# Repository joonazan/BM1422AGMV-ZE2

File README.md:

# Magnetic position tracking

Code for finding the position of a magnetometer or a coil relative to electromagnets in a fixed arrangement.

The process consists of two phases: determining each magnet's field strength at the measuring device and computing the position of the measuring device based on that.

## Finding each magnet's field strength at the position of interest

The main problem is isolating a single magnet's field from the earth's magnetic field, noise and the other magnets. This is not possible with just one point of data. One has to have multiple points of measurement or a sequence of measurements.

This project drives each magnet with a different sine wave. One only has to isolate the correct frequency from the magnetic field measurements.

### On magnetometers

Magnetometers are very small and thus easy to attach and unobtrusive. They could even be part of some cyberpunk nail art. But it is hard to find a suitable one for this purpose. I suspect that is because they are mostly meant for mobile phones.

The BM1422AGMV-ZE2 is the best one I could find. It can be set up to measure with 14-bit accuracy at one kilohertz.

The accuracy directly affects the accuracy of the position. Note that the difference between a magnet's positive and negative peak gets smaller and smaller with distance, so only a small part of the scale may be in use at one time.

The sample rate affects latency and accuracy while moving. Think about the Discrete Fourier Transform. With eight samples one would get one frequency bucket per magnet, the bare minimum. With more samples noise is filtered out.

We know the phase of the sine waves, which may help do more with less samples. I haven't investigated this.

One more pain point of magnetometers reading the data. The BM1422AGMV-ZE only supports two different I²C addresses, so each pair of them takes up one bus. They only support a 400kHz clock, too, so the bus is saturated.

### Isolating the frequencies

The signal processing happens on the chip that reads the magnetometers, as it is computationally inexpensive and reduces the amount of data by an order of magnitude. The code for the microprocessor is in `magnetometer_peripheral`.

A magnetometer measures the magnetic field on three perpendicular axes. The readings are not centered around zero magnetic field and changing the hardware in the slightest offsets them. Because of that, we cannot compute the unfiltered field strength with the Pythagorean Theorem. Each axis is filtered separately and then combined. This happens in `field_strength.h`.

The filtering is done using an algorithm that keeps a single DFT bucket up to date. Updating the bucket based on a new sample is O(1) regardless of DFT size. The buckets can be centered around any value but their window width depends on DFT size as usual. "The sliding DFT" (IEEE Signal Processing Magazine, April 2003) is a very detailed and readable explanation of the algorithm.

### Using a coil instead?

The receivers could be coils. Coils are larger than magnetometers and can have a bit more personality. However, with the correct circuit, they are not limited by a sample rate. That means that they can receive very high frequencies, which means low latency and low noise.

## Generating sines

`sine_pwm_no_arduino` contains the code that I've used on my Arduino Uno to generate sine waves via PWM. `flash.sh` is what I used to flash. The commands should be pretty straightforward to adapt to any platform.

I don't use the Arduino IDE because its compiler flags prevent me from generating a sine table in a sane way. `sine_pwm` is the same but uses ugly templates for sine table generation.

Both versions use Timer 0 and 2 and fire 250 000 interrupts per second to get very high frequency PWM. That may interfere with using the Arduino for other purposes.

The output needs to be smoothed with a low-pass filter and amplified.

A sine generator circuit could be used instead but it probably wouldn't even be cheaper than a cheap SoC. When using coils as receivers, a sine circuit is superior because this method can only go up to about 1 kHz with good quality.

## Finding the position

A point is uniquely determined by its distance from n points, where n is the number of dimensions plus one. For example in two dimensions two circles can intersect at two points, but three different circles can only intersect at one point.

`amplitude_to_position` is used to test and compare different algorithms for finding the point from which the magnet's strengths were measured.

There would be a simple exact solution if the fields spread out in a sphere (as is the case with GPS). However, only magnetic monopoles would have a spherical field. The field of a coil has a circular cross-section but the equation for its radius is fourth-degree.

TODO insert image of field shape

The same testbed can also be used to automatically compare different placements of magnets and thus find an optimal placement for a given level of noise and placement constraints.

TODO Some kind of Gradient descent probably works but I haven't tried it yet
TODO What about partitioning the cube root of field strength space?

### What doesn't work

The following two methods work perfectly if the measurements are perfectly accurate. But for high accuracy in practice a method is required that reacts gracefully to error.

#### Space partitioning

Implemented in `octtree.rs`. Finds the smallest cube that contains points with the correct field strength for each magnet.

Split cubes into smaller cubes. Keep the cubes that are still good.

Bad because:

- Splitting the optimal cube creates two cubes that are rejected.
- Performance is relatively bad and unpredictable. May allocate a lot. Performance may be better with a depth-first traversal rather than breadth-first.

#### Slicing

Implemented in `slicer.rs`. Slices the problem into a bunch of very cheaply solved circle intersection problems, takes the slice with least error.

I define the *scale* as `1 / cbrt(field strength)`. That is how much you have to scale the field strength = 1 surface to get the surface for that field strength.

The biggest possible slope of the error (in scale) vs. z is `4 / cbrt(2)`, which occurs when moving up when directly above the pole of all four magnets. The best solution is of course the same or better.

Bad because:

- Can only support configurations where all magnets point the same way.
- The slices' solutions are not optimal. You can see in the illustration that the inner isosurfaces are further apart along the red line than the outer ones. So the error is proportional to change in radius only at height zero. 

There is still some hope for this if there is a way to find the best solution to a slice. Quality could be improved just by taking into account that increasing radius is cheaper higher up.

## Running the whole stack

The Arduino MKR Wifi 1010 can be flashed with the Arduino IDE. FastBLE and I2C_DMAC are required because the official ones can't be used asynchronously. FastBLE includes a part that needs to be flashed onto the ESP side of the board. See its README.

Two BM1422AGMV-ZE magnetometers with address select wired differently can be attached to pins 11 (SDA here) and 12 (SCL here). TODO update once the other two pins pairs are used as well. (Should make it detect what pins have a device on them)

TODO write about computer side after I've worked with it again

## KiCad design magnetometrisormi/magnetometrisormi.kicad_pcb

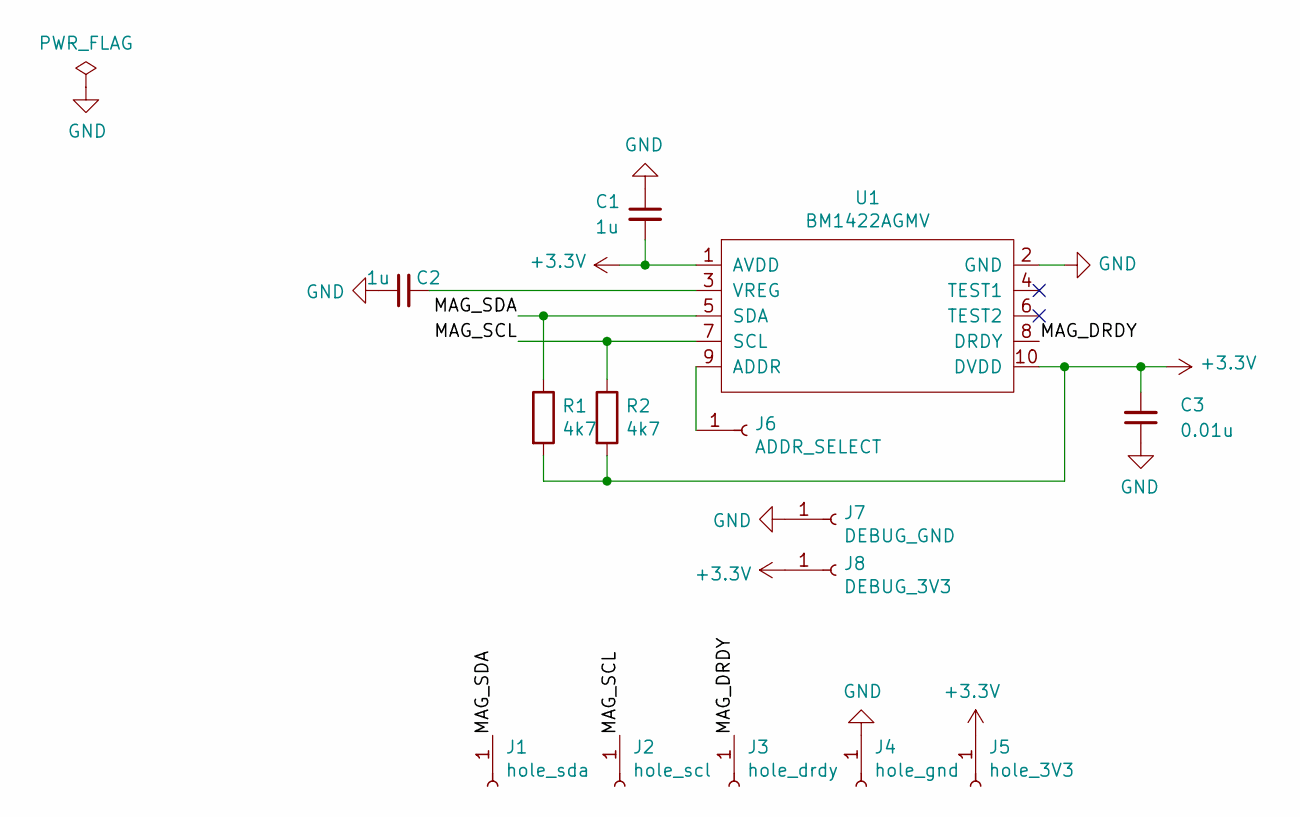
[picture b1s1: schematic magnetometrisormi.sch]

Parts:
C1, C2: 1u; C_0402_1005Metric
C3: 0.01u; C_0402_1005Metric
J1: hole_sda; hole
J2: hole_scl; hole
J3: hole_drdy; hole
J4: hole_gnd; hole
J5: hole_3V3; hole
J6: ADDR_SELECT; hole
J7: DEBUG_GND; hole
J8: DEBUG_3V3; hole
R1, R2: 4k7; R_0402_1005Metric
U1: BM1422AGMV; MLGA010V020A

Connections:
+3V3: C1.2, C3.2, J5.1, J8.1, R1.2, R2.2, U1.1 (AVDD), U1.10 (DVDD)
/MAG_DRDY: J3.1, U1.8 (DRDY)
/MAG_SCL: J2.1, R2.1, U1.7 (SCL)
/MAG_SDA: J1.1, R1.1, U1.5 (SDA)
GND: C1.1, C2.1, C3.1, J4.1, J7.1, U1.2 (GND)
unnamed: C2.2, U1.3 (VREG)
unnamed: J6.1, U1.9 (ADDR)

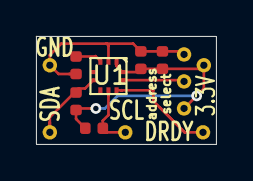
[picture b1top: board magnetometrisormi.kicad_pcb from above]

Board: 2 copper layers, 10.0 x 6.0 mm, 14 parts (0 on the bottom side), 7 nets.

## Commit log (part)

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2019-09-26 bias selection for magnetometer
2019-10-01 show some magnetometer readings
2019-10-10 generate two different sines
2019-10-11 actually output two sines
2019-10-11 record and display fft of magnetometer data
2019-10-17 use continous 1kHz measurement
    At this point the Python script can't keep up. Either there is
    too much overhead from Python, or the bus can't transfer all the requests
    for x, y and z in time and one should instead just read without sending
    requests.
2019-10-17 remove unnecessary file opening
2019-10-17 measuring time to get a reading in C
    The C code gets good values, but it alternates between hundreds of
    slow measurements and hundreds of correctly timed measurements.
2019-10-17 timing fixed by increasing baudrate
    The I2C baudrate is now the maximum of 400kHz. (This is a raspberry pi
    setting) There is still some jitter. To remove it, DRDY should be soldered.
2019-10-17 read measurements exactly 1ms apart
    This might drift away from the magnetometer's clock if run for long
    enough so attaching DRDY may be better in the long run.
2019-10-17 get the strength of each electromagnet
    I checked with a graph and the vast majority of it is on exactly
    the right frequency!
2019-10-18 document why the fft bins are indexed by frequency
2019-10-21 fixed sensor setup in C version
    Each register write has to be made with a separate write call.
2019-10-24 live_plot gets sensor readings from stdin
    At this point the output is just numbers
2019-10-24 show_fft takes filename argument and doesn't plot
    I've been using gnuplot instead, as it works better
2019-10-24 four sines WIP
2019-10-25 four sines with adjustable frequency
    The ISR is too slow. The sine quality is bad when driving more than two
    at at time.
2019-10-25 sine_pwm_no_arduino
    Not using the Arduino IDE gives C++14 and more freedom.
    Beign able to compile with O2 helps a bit.
    The only thing I used from the Arduino library was pinMode.
2019-10-25 draw n circle live plot
2019-10-25 show_fft takes filename, but plots
2019-10-25 remove unnecessary register saving from ISR
2019-10-25 store counters in registers
2019-11-06 more accurate positions of the electromagnets
2019-11-06 add recordings to test algorithms withtout the actual hardware
2019-11-27 record square with new amplified circuit
    5x5 square square and coils 5 squares apart, see image below
    c
    |
    a - b
    a, b, c are in that order when computing distances with live_plot.py
2019-12-09 add mathematica notebook for prototype graphing
2019-12-10 add 3d model of magnet holder
2020-01-08 precompute the next value into registers
    When the interrupt fires, the new values are just copied from
    registers.
    Then the next values are precomputed.
    You can't get lower latency than this.
2020-01-09 fast 2d position calculation with plotting
2020-01-09 real time plotting to window
2020-01-10 add config file
2020-01-10 draw magnets in a scale-independent way
2020-01-10 find parameters for current magnet holder
2020-01-23 quadtree -> octtree
2020-01-27 fix zero division error
2020-01-27 configure for four magnets
    This also fixes a bug that prevented having any other number of magnets than
    three.
    Note: running the program with just three magnets can hang, as there are an
    infinite number of valid positions then. I should limit the number of
    AABBs checked instead of the number of subdivisions.
2020-01-28 draw top and side view
2020-01-28 plot field contribution from each magnet
2020-02-05 communication over bluetooth GATT
2020-03-11 magnetometer readings over BLE but too slow
    ArduinoBLE must be replaced by my own FastBLE
2020-03-13 convert to use my own bluetooth library
2020-03-25 use asynchronous I2C library
2020-03-30 make client build more reproducible; update uuid
2020-04-08 fix bug in field strength calculation
    This will affect the results dramatically.
    Also changed it to a dot product with the direction the magnet's north
    is pointing to because we will want to test magnets that are not
    perfectly aligned.
2020-04-08 added code for Sliding DFT
    Not sure if this will be used in the end.
2020-04-14 directly compute the maximum field strength
    The part of the cube where the magnetic field is strongest is simple to
    find. It is not necessary to enumerate all critical points.
2020-04-14 use inclusive ranges to represent AABBs
2020-04-14 test the new optimization with quickcheck
2020-04-14 find field strength minimum faster
    While I haven't rigorously proven this method, the test passes
    with QUICKCHECK_TESTS=1000000.
2020-04-14 refactor field strength maximum computation
    Now the field strength range computation is about as fast as it can get.
    Further improvement could come from sharing computation between parent
    and child but the potential gain is low (1/8) and it would make the code
    more complex.
2020-04-15 faster way to calculate the cosine
    The idea with the dot product was that the code could support
    magnets pointing in different directions but that doesn't work
    with the current code, so no reason to support it in that one place.
2020-04-15 got rid of square root
    This improved accuracy so much that I cannot get the quickcheck test to
    fail anymone.
2020-04-20 exclude the test from Arduino IDE build
2020-04-20 simplify Comb
2020-04-20 document Sliding DFT implementation
2020-04-20 Resonator takes frequency instead of bucket
    The user no longer has to calculate the DFT bucket. They can just input
    frequency / sample rate.
    This also gets rid of one unnecessary division in the constructor.
2020-04-20 remove recording for some old magnet arrangement
2020-04-20 move code from .ino to .cpp
2020-04-20 code that computes each magnet's field strength at a sensor
2020-04-20 move magnetometer-specific code into its own file
2020-05-20 make tests work
2020-05-20 Newton's method for finding radius at certain z
    Works, except directly above, as Newton's method doesn't work for zeros
    with a derivative of zero.
2020-05-25 compare two implementations
2020-05-25 Use Halley's method instead of newton's method
    I believe the accuracy is good enough now, but the quickcheck test needs
    to be improved to be absolutely sure.
2020-05-26 implement 2d case
2020-05-26 write test for whole transformation
2020-05-26 naive slicing implementation complete
    Naive in the sense that it linearly samples the whole range of possible
    z. This is horribly inefficient and inaccurate, as z requires sampling
    at that resolution.
2020-05-27 clearer output
2020-05-27 subdivide octtree till epsilon
    With this change the octtree method will never stop subdividing too
    early.
    The naive slicer still sometimes outperforms it, which validates my
    hypothesis that subdivision often doesn't converge on the best location.
2020-05-27 tighter Z-bounds for slicer
    This makes it fairly consistently more accurate than occttree
2020-05-28 get rid of division in 2d solution
2020-05-28 bake multipliers into precomputed values
2020-05-28 premultiply offset
2020-06-11 write first draft of top-level documentation
2020-07-07 remove files that are not needed or don't work
2020-07-08 do signal processing on Arduino instead of PC
2020-07-08 choose better frequencies
2020-07-08 cargo fmt and clippy
2020-07-08 dynamic step size for slicer
2020-07-09 sine_pwm: add C++14 compilation flag
    Makes it compile on older compilers
2020-07-09 explicitly use py3 in run.sh
2020-07-09 use half step in slicer
    This makes it somewhat ok. The correct step size cannot be used
    because the slice solutions are incorrect as explained in the README
2020-07-09 client now can use any of the backends in amplitude_to_position
2020-07-09 add schematics for magnetometer circuit board
2020-07-09 Create LICENSE
2022-06-06 Bump nalgebra from 0.21.0 to 0.27.1 in /amplitude_to_position
    Bumps [nalgebra](https://github.com/dimforge/nalgebra) from 0.21.0 to 0.27.1.
    - [Release notes](https://github.com/dimforge/nalgebra/releases)
    - [Changelog](https://github.com/dimforge/nalgebra/blob/dev/CHANGELOG.md)
    - [Commits](https://github.com/dimforge/nalgebra/compare/v0.21.0...v0.27.1)
    ---
    updated-dependencies:
2022-06-06 Bump crossbeam-deque from 0.7.2 to 0.7.4 in /client/haarukointi
    Bumps [crossbeam-deque](https://github.com/crossbeam-rs/crossbeam) from 0.7.2 to 0.7.4.
    - [Release notes](https://github.com/crossbeam-rs/crossbeam/releases)
    - [Changelog](https://github.com/crossbeam-rs/crossbeam/blob/master/CHANGELOG.md)
    - [Commits](https://github.com/crossbeam-rs/crossbeam/compare/crossbeam-deque-0.7.2...crossbeam-deque-0.7.4)
    ---
    updated-dependencies:
2022-06-06 Bump generic-array from 0.13.2 to 0.13.3 in /amplitude_to_position
    Bumps [generic-array](https://github.com/fizyk20/generic-array) from 0.13.2 to 0.13.3.
    - [Release notes](https://github.com/fizyk20/generic-array/releases)
    - [Changelog](https://github.com/fizyk20/generic-array/blob/0.13.3/CHANGELOG.md)
    - [Commits](https://github.com/fizyk20/generic-array/compare/0.13.2...0.13.3)
    ---
    updated-dependencies:
2022-06-06 Bump bumpalo from 3.1.2 to 3.10.0 in /client/haarukointi
    Bumps [bumpalo](https://github.com/fitzgen/bumpalo) from 3.1.2 to 3.10.0.
    - [Release notes](https://github.com/fitzgen/bumpalo/releases)
    - [Changelog](https://github.com/fitzgen/bumpalo/blob/main/CHANGELOG.md)
    - [Commits](https://github.com/fitzgen/bumpalo/commits)
    ---
    updated-dependencies:
2022-06-08 Bump ordered-float from 1.0.2 to 1.1.1 in /client/haarukointi
    Bumps [ordered-float](https://github.com/reem/rust-ordered-float) from 1.0.2 to 1.1.1.
    - [Release notes](https://github.com/reem/rust-ordered-float/releases)
    - [Commits](https://github.com/reem/rust-ordered-float/compare/v1.0.2...v1.1.1)
    ---
    updated-dependencies:
    - dependency-name: ordered-float
2022-06-17 Bump crossbeam-queue from 0.2.1 to 0.2.3 in /client/haarukointi
    Bumps [crossbeam-queue](https://github.com/crossbeam-rs/crossbeam) from 0.2.1 to 0.2.3.
    - [Release notes](https://github.com/crossbeam-rs/crossbeam/releases)
    - [Changelog](https://github.com/crossbeam-rs/crossbeam/blob/master/CHANGELOG.md)
    - [Commits](https://github.com/crossbeam-rs/crossbeam/compare/crossbeam-queue-0.2.1...crossbeam-queue-0.2.3)
    ---
    updated-dependencies:
2022-06-17 Bump smallvec from 0.6.13 to 0.6.14 in /client/haarukointi
    Bumps [smallvec](https://github.com/servo/rust-smallvec) from 0.6.13 to 0.6.14.
    - [Release notes](https://github.com/servo/rust-smallvec/releases)
    - [Commits](https://github.com/servo/rust-smallvec/compare/v0.6.13...v0.6.14)
    ---
    updated-dependencies:
    - dependency-name: smallvec
2022-06-17 Bump thread_local from 1.0.1 to 1.1.4 in /amplitude_to_position
    Bumps [thread_local](https://github.com/Amanieu/thread_local-rs) from 1.0.1 to 1.1.4.
    - [Release notes](https://github.com/Amanieu/thread_local-rs/releases)
    - [Commits](https://github.com/Amanieu/thread_local-rs/compare/v1.0.1...1.1.4)
    ---
    updated-dependencies:
    - dependency-name: thread_local
2022-06-17 Bump thread_local from 1.0.1 to 1.1.4 in /client/haarukointi
    Bumps [thread_local](https://github.com/Amanieu/thread_local-rs) from 1.0.1 to 1.1.4.
    - [Release notes](https://github.com/Amanieu/thread_local-rs/releases)
    - [Commits](https://github.com/Amanieu/thread_local-rs/compare/v1.0.1...1.1.4)
    ---
    updated-dependencies:
    - dependency-name: thread_local
